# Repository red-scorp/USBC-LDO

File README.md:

# USBC-LDO Project

The **USBC-LDO** project is a aimed to create low-cost DIY board with USB-C with LDO power supply.

## USBC-LDO Board

The **USBC-LDO** is simple board that provides a USB-C connector and a low-dropout voltage regulator (LDO) to power a small device from a USB-C power source. The board is designed to be as small as possible and to be used in a variety of applications where a small, low-cost, and easy-to-use power supply is needed.

Current design is based on the [LM1117](https://www.ti.com/lit/ds/symlink/lm1117.pdf) LDO voltage regulator, which can provide up to 1A of output current at 3.3V. However, the board can be easily modified to use a different LDO voltage regulator if needed.

Preview:

You can view the [Schematics in PDF format](doc/USBC-LDO.pdf) for detailed information.

STEP 3D file is available [here](doc/USBC-LDO.step).

Features:

- USB-C connector configured for 5V power delivery
- 3.3V LDO voltage regulator up to 1A output current
- LED power indicator

CAM files, as well as the BOM and CPL files for JLCPCB and NextPCB, are available.

## Version History

### v1.0

Initial release.

## Links

- TBD

## How to Help

Your contributions as code, resources, or finances are welcome! Please contact me directly via email at andriy.golovnya@gmail.com or through my [GitHub profile](https://github.com/red-scorp).

If you'd like to make a financial contribution, you can donate via [PayPal](http://paypal.me/redscorp) or [Ko-Fi](http://ko-fi.com/redscorp). Your support is greatly appreciated.

Thanks in advance!

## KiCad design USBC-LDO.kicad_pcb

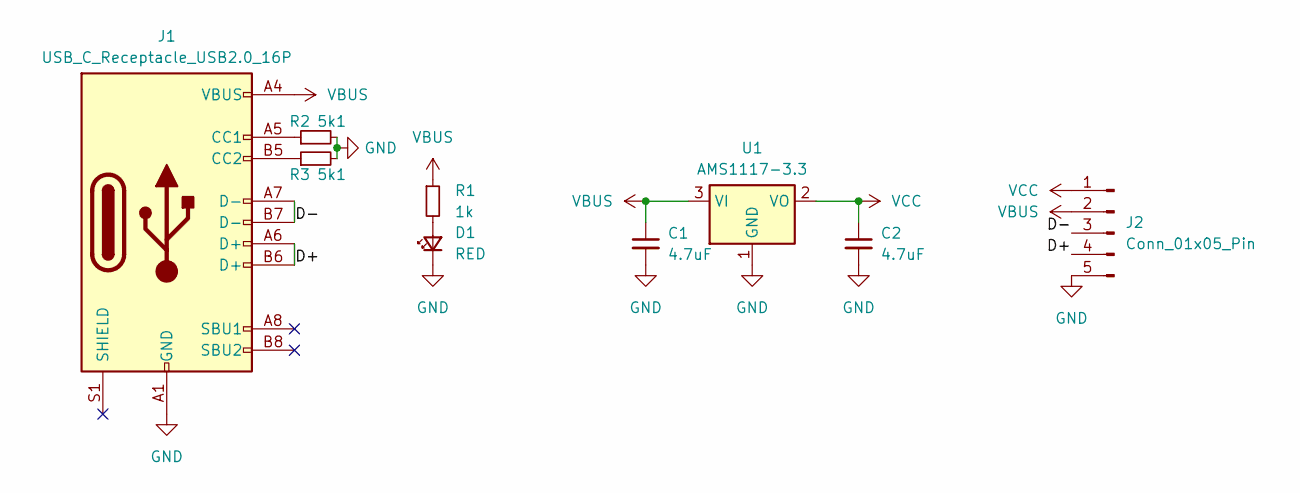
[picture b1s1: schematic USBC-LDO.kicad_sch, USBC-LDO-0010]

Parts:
C1, C2: 4.7uF; C_0805_2012Metric
D1: RED; LED_0603_1608Metric
J1: USB_C_Receptacle_USB2.0_16P; USB_C_Receptacle_HRO_TYPE-C-31-M-12
J2: Conn_01x05_Pin; PinHeader_1x05_P2.54mm_Vertical
R1: 1k; R_0402_1005Metric
R2, R3: 5k1; R_0402_1005Metric
U1: AMS1117-3.3; SOT-223-3_TabPin2

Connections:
/D+: J1.A6 (D+), J1.B6 (D+), J2.4
/D-: J1.A7 (D-), J1.B7 (D-), J2.3
GND: C1.2, C2.2, D1.1 (K), J1.A1 (GND), J1.A12 (GND), J1.B1 (GND), J1.B12 (GND), J2.5, R2.2, R3.2, U1.1 (GND)
unnamed: D1.2 (A), R1.2
unnamed: J1.A5 (CC1), R2.1
unnamed: J1.B5 (CC2), R3.1
VBUS: C1.1, J1.A4 (VBUS), J1.A9 (VBUS), J1.B4 (VBUS), J1.B9 (VBUS), J2.2, R1.1, U1.3 (VI)
VCC: C2.1, J2.1, U1.2 (VO)

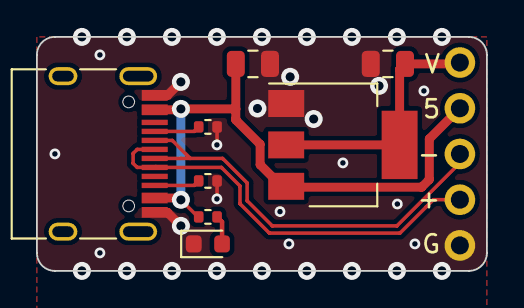
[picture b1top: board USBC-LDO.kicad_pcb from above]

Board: 2 copper layers, 25.0 x 13.0 mm, 9 parts (0 on the bottom side), 8 nets.

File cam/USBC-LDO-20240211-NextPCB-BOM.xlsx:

Designator | Qty | Manufacturer Part Number | Customer Supply | Customer Remark
C2,C1 | 2 | CL21A475KAQNNNE | -- | 4.7uF
R1 | 1 | 0402WGF1001TCE | -- | 1k
R3,R2 | 2 | 0402WGF5101TCE | -- | 5k1
D1 | 1 | KT-0603R | -- | RED
U1 | 1 | AMS1117-3.3 | -- | AMS1117-3.3
J1 | 1 | TYPE-611-T3-W | -- | USB_C_Receptacle_USB2.0_16P

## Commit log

2024-02-11 Added basic structure
2024-02-11 Added proper 3D model for USB-C port.
2024-02-11 Generated PDF schematics
2024-02-11 Generated STEP 3D model
2024-02-11 Fixed missing trace
2024-02-11 Generated PNG preview
2024-02-11 Generated CAM files
2024-02-11 Generated BOM and CPL files
2024-02-24 Added NextPCB CAM and BOM files
2024-02-26 Generated PnP files for NextPCB
2024-03-10 Added README.md
2024-03-10 Fixed a typo
